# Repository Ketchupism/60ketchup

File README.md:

# 60ketchup
60% keyboard gasket-mount with hot-swaps

most effort-keyboard project I made

- 61 keys (number keys, no arrows keys)
- hot-swaps
- gasket-mount

I started with project somewhat weeks ago after finishing my first keyboard. There was so many improvements and changes I could of make if I made another keyboard. I tried to make a curved Alice, split wired keyboard. Unfortunately, I ended up with not many days to work on it and time was running out before the program ended. I had to edit my schematics and PCB to fit the new keyboard criteria. I spent the rest of the days just then working on the PCB and github. 

Overall, this project was fun and gave me opportunities to practice and learn using Fusion360 and KiCad and the general understanding of how keyboards are made. Learning how to create a keyboard and having a finished product that I was satisfied with was really nice. Some of the things that were a huge process or took a long time to learn / work on was reediting work to a new keyboard layout, tracing all my components, learning how to create a gasket mount that was stable, and creating my bill of materials list. My files are found in PCB and KiCad.

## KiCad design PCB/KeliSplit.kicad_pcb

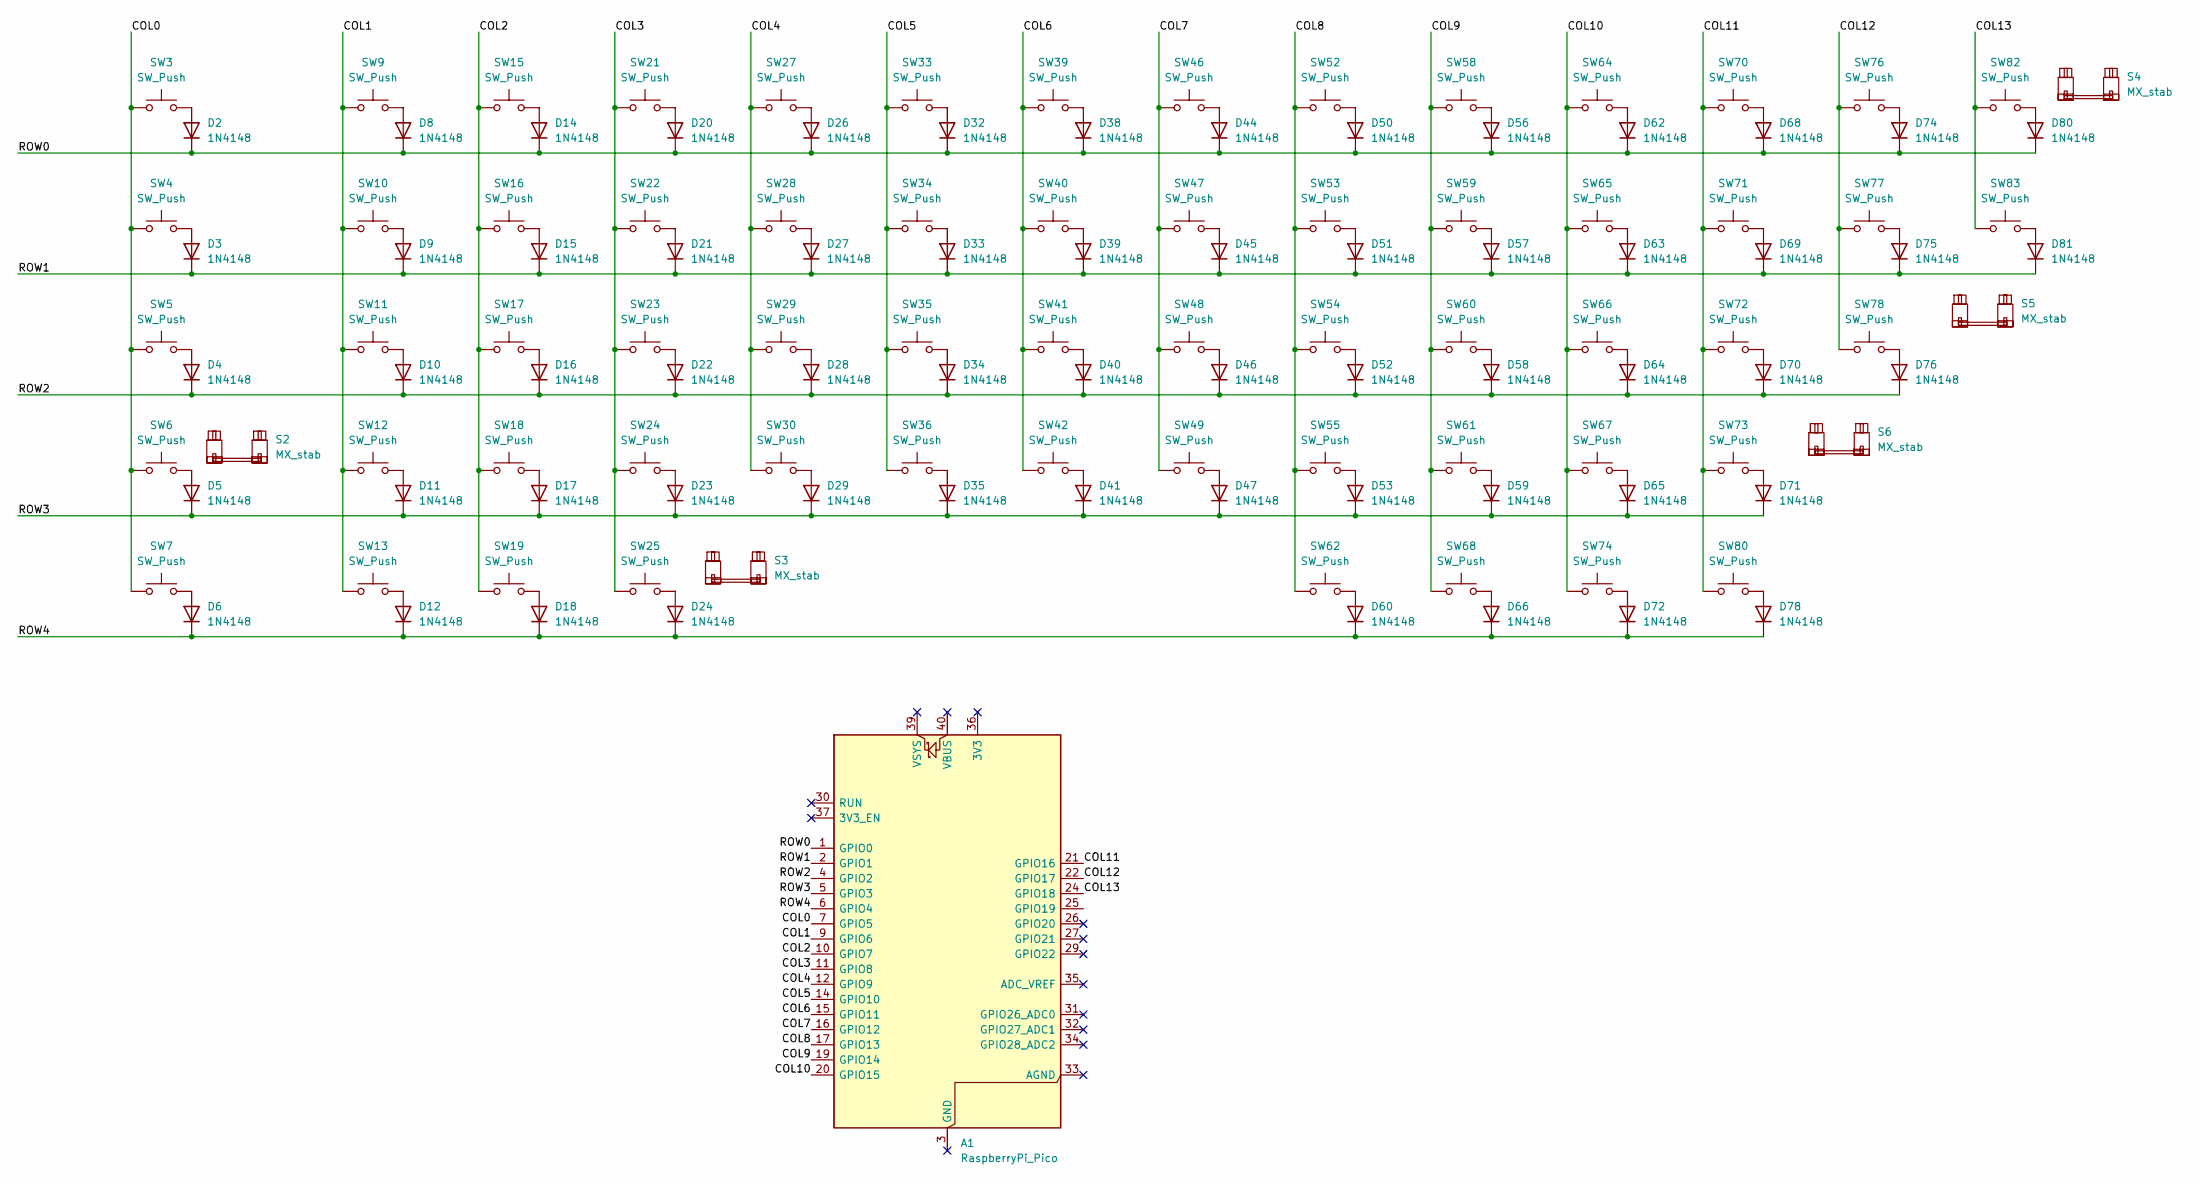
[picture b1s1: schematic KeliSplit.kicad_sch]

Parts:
A1: RaspberryPi_Pico; RaspberryPi_Pico_Common_THT
D2, D3, D4, D5, D6, D8, D9, D10, D11, D12, D14, D15, D16, D17, D18, D20, D21, D22, D23, D24, D26, D27, D28, D29, D32, D33, D34, D35, D38, D39, D40, D41, D44, D45, D46, D47, D50, D51, D52, D53, D56, D57, D58, D59, D60, D62, D63, D64, D65, D66, D68, D69, D70, D71, D72, D74, D75, D76, D78, D80, D81: 1N4148; D_DO-35_SOD27_P7.62mm_Horizontal
S2, S5: MX_stab; STAB_MX_P_2.25u
S3: MX_stab; STAB_MX_P_6.25u
S4: MX_stab; STAB_MX_P_2u
S6: MX_stab; STAB_MX_P_2.75u
SW3, SW6, SW9, SW10, SW11, SW12, SW15, SW16, SW17, SW18, SW21, SW22, SW23, SW24, SW25, SW27, SW28, SW29, SW30, SW33, SW34, SW35, SW36, SW39, SW40, SW41, SW42, SW46, SW47, SW48, SW49, SW52, SW53, SW54, SW55, SW58, SW59, SW60, SW61, SW64, SW65, SW66, SW67, SW70, SW71, SW72, SW73, SW76, SW77, SW78, SW82: SW_Push; SW_MX_HS_CPG151101S11_1u
SW4, SW83: SW_Push; SW_MX_HS_CPG151101S11_1.5u
SW5: SW_Push; SW_MX_HS_CPG151101S11_1.75u
SW7, SW13, SW19, SW62, SW68, SW74, SW80: SW_Push; SW_MX_HS_CPG151101S11_1.25u

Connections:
/COL0: A1.7 (GPIO5), SW3.1, SW4.1, SW5.1, SW6.1, SW7.1
/COL1: A1.9 (GPIO6), SW9.1, SW10.1, SW11.1, SW12.1, SW13.1
/COL2: A1.10 (GPIO7), SW15.1, SW16.1, SW17.1, SW18.1, SW19.1
/COL3: A1.11 (GPIO8), SW21.1, SW22.1, SW23.1, SW24.1, SW25.1
/COL4: A1.12 (GPIO9), SW27.1, SW28.1, SW29.1, SW30.1
/COL5: A1.14 (GPIO10), SW33.1, SW34.1, SW35.1, SW36.1
/COL6: A1.15 (GPIO11), SW39.1, SW40.1, SW41.1, SW42.1
/COL7: A1.16 (GPIO12), SW46.1, SW47.1, SW48.1, SW49.1
/COL8: A1.17 (GPIO13), SW52.1, SW53.1, SW54.1, SW55.1, SW62.1
/COL9: A1.19 (GPIO14), SW58.1, SW59.1, SW60.1, SW61.1, SW68.1
/COL10: A1.20 (GPIO15), SW64.1, SW65.1, SW66.1, SW67.1, SW74.1
/COL11: A1.21 (GPIO16), SW70.1, SW71.1, SW72.1, SW73.1, SW80.1
/COL12: A1.22 (GPIO17), SW76.1, SW77.1, SW78.1
/COL13: A1.24 (GPIO18), SW82.1, SW83.1
/ROW0: A1.1 (GPIO0), D2.1 (K), D8.1 (K), D14.1 (K), D20.1 (K), D26.1 (K), D32.1 (K), D38.1 (K), D44.1 (K), D50.1 (K), D56.1 (K), D62.1 (K), D68.1 (K), D74.1 (K), D80.1 (K)
/ROW1: A1.2 (GPIO1), D3.1 (K), D9.1 (K), D15.1 (K), D21.1 (K), D27.1 (K), D33.1 (K), D39.1 (K), D45.1 (K), D51.1 (K), D57.1 (K), D63.1 (K), D69.1 (K), D75.1 (K), D81.1 (K)
/ROW2: A1.4 (GPIO2), D4.1 (K), D10.1 (K), D16.1 (K), D22.1 (K), D28.1 (K), D34.1 (K), D40.1 (K), D46.1 (K), D52.1 (K), D58.1 (K), D64.1 (K), D70.1 (K), D76.1 (K)
/ROW3: A1.5 (GPIO3), D5.1 (K), D11.1 (K), D17.1 (K), D23.1 (K), D29.1 (K), D35.1 (K), D41.1 (K), D47.1 (K), D53.1 (K), D59.1 (K), D65.1 (K), D71.1 (K)
/ROW4: A1.6 (GPIO4), D6.1 (K), D12.1 (K), D18.1 (K), D24.1 (K), D60.1 (K), D66.1 (K), D72.1 (K), D78.1 (K)
unnamed: D2.2 (A), SW3.2
unnamed: D3.2 (A), SW4.2
unnamed: D4.2 (A), SW5.2
unnamed: D5.2 (A), SW6.2
unnamed: D6.2 (A), SW7.2
unnamed: D8.2 (A), SW9.2
unnamed: D9.2 (A), SW10.2
unnamed: D10.2 (A), SW11.2
unnamed: D11.2 (A), SW12.2
unnamed: D12.2 (A), SW13.2
unnamed: D14.2 (A), SW15.2
unnamed: D15.2 (A), SW16.2
unnamed: D16.2 (A), SW17.2
unnamed: D17.2 (A), SW18.2
unnamed: D18.2 (A), SW19.2
unnamed: D20.2 (A), SW21.2
unnamed: D21.2 (A), SW22.2
unnamed: D22.2 (A), SW23.2
unnamed: D23.2 (A), SW24.2
unnamed: D24.2 (A), SW25.2
unnamed: D26.2 (A), SW27.2
unnamed: D27.2 (A), SW28.2
unnamed: D28.2 (A), SW29.2
unnamed: D29.2 (A), SW30.2
unnamed: D32.2 (A), SW33.2
unnamed: D33.2 (A), SW34.2
unnamed: D34.2 (A), SW35.2
unnamed: D35.2 (A), SW36.2
unnamed: D38.2 (A), SW39.2
unnamed: D39.2 (A), SW40.2
unnamed: D40.2 (A), SW41.2
unnamed: D41.2 (A), SW42.2
unnamed: D44.2 (A), SW46.2
unnamed: D45.2 (A), SW47.2
unnamed: D46.2 (A), SW48.2
unnamed: D47.2 (A), SW49.2
unnamed: D50.2 (A), SW52.2
unnamed: D51.2 (A), SW53.2
unnamed: D52.2 (A), SW54.2
unnamed: D53.2 (A), SW55.2
unnamed: D56.2 (A), SW58.2
unnamed: D57.2 (A), SW59.2
unnamed: D58.2 (A), SW60.2
unnamed: D59.2 (A), SW61.2
unnamed: D60.2 (A), SW62.2
unnamed: D62.2 (A), SW64.2
unnamed: D63.2 (A), SW65.2
unnamed: D64.2 (A), SW66.2
unnamed: D65.2 (A), SW67.2
unnamed: D66.2 (A), SW68.2
unnamed: D68.2 (A), SW70.2
unnamed: D69.2 (A), SW71.2
unnamed: D70.2 (A), SW72.2
unnamed: D71.2 (A), SW73.2
unnamed: D72.2 (A), SW74.2
unnamed: D74.2 (A), SW76.2
unnamed: D75.2 (A), SW77.2
unnamed: D76.2 (A), SW78.2
unnamed: D78.2 (A), SW80.2
unnamed: D80.2 (A), SW82.2
unnamed: D81.2 (A), SW83.2

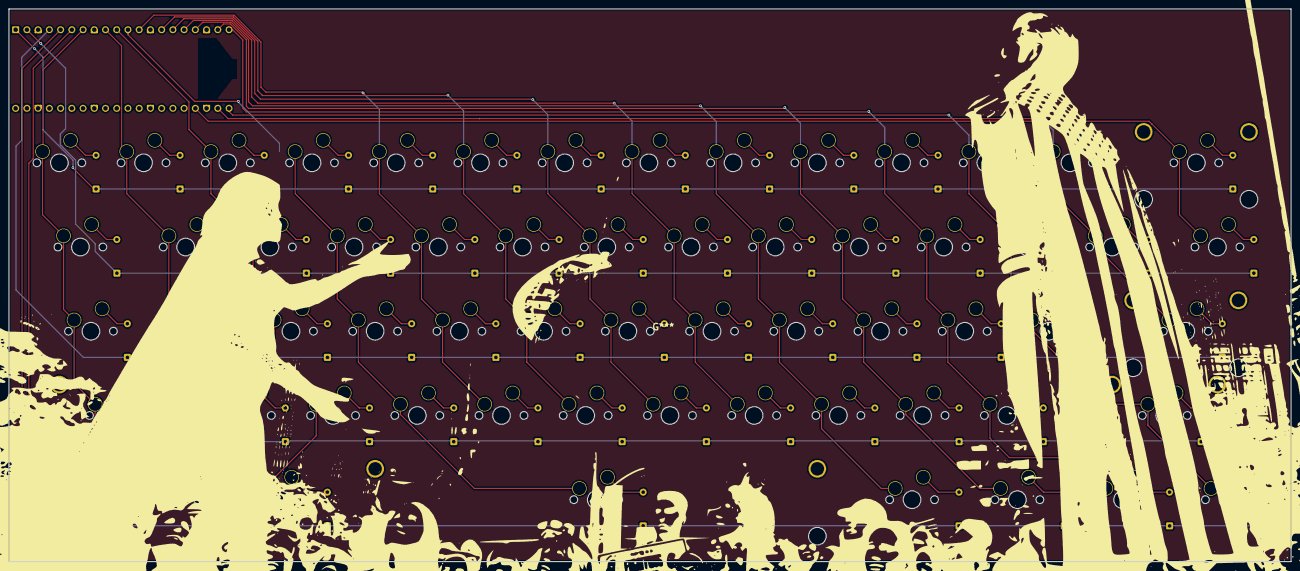
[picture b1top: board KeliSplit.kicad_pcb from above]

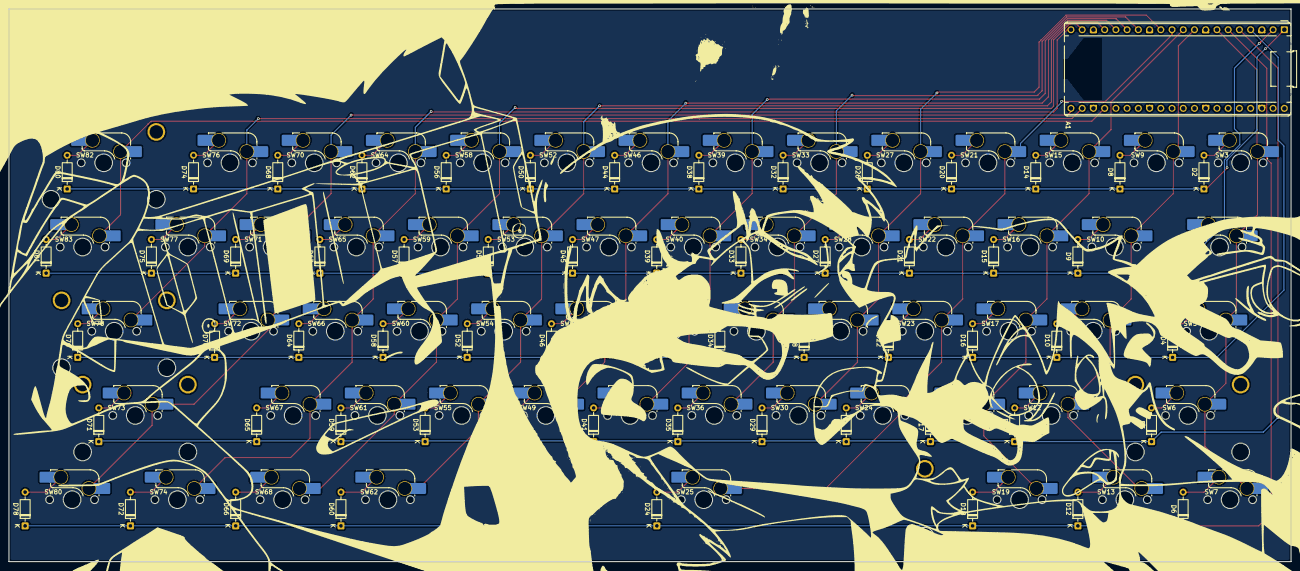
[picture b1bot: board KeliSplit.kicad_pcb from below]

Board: 2 copper layers, 290.0 x 125.0 mm, 128 parts (123 on the bottom side), 80 nets.
